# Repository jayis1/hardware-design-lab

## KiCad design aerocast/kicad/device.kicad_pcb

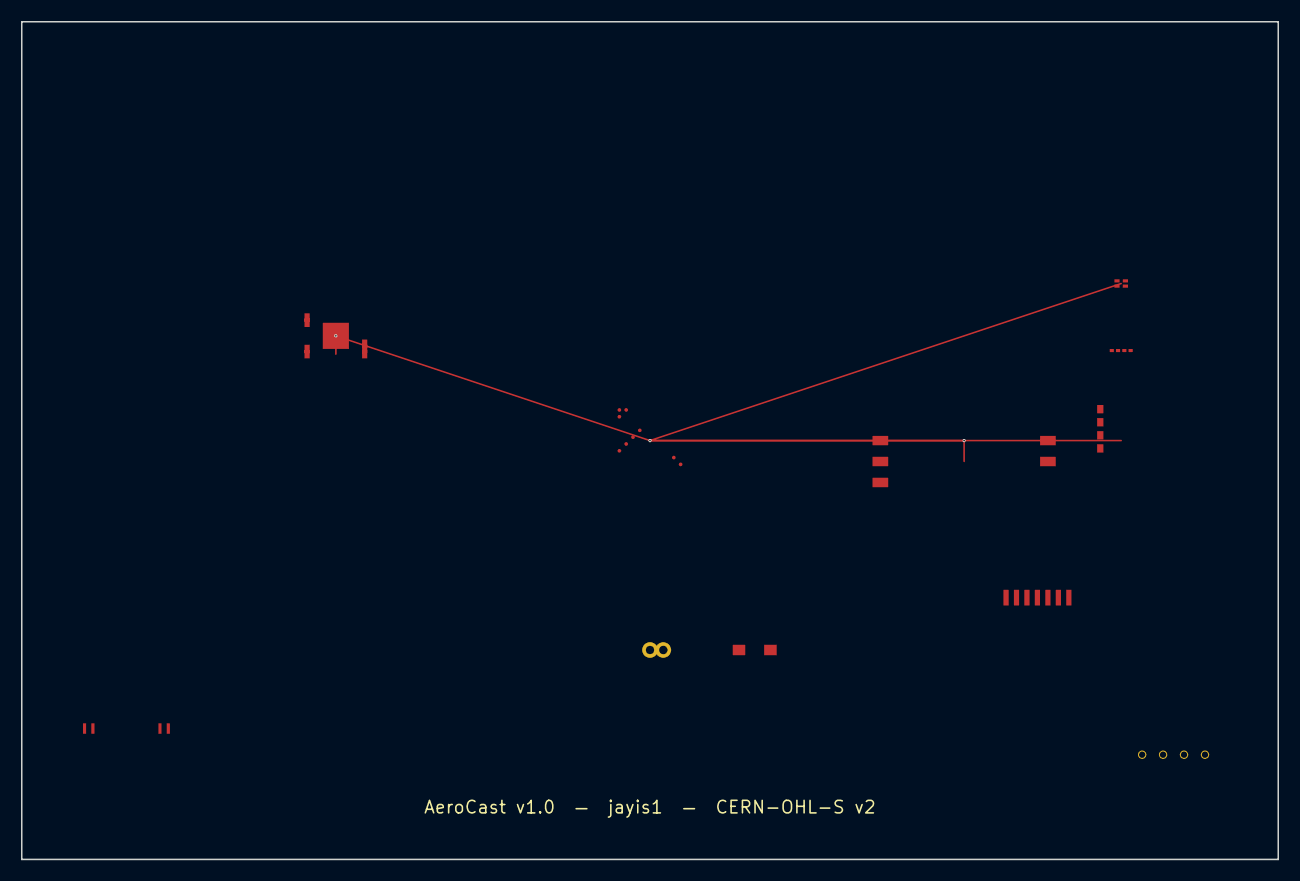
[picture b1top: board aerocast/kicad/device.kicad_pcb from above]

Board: 4 copper layers, 120.0 x 80.0 mm, 11 parts (0 on the bottom side), 9 nets.

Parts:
D1: 650nm_50mW; TO-18_3Pin
D2: 340nm_300mW; LED_3528
DISP1: ST7789V_240x320; ST7789V_2.4in_FPC_10pin
J1: USB-C; USB_C_Receptacle_HRO_TYPE-C-31-M-12
J4: Anemometer_RS485; JST_PH_B4B-PH-K_1x04_P2.00mm_Vertical
U1: STM32H7A3VIT6; UFBGA-176_10x10mm_P0.65mm
U2: ESP32-C6-MINI-2U
U3: LTC2351-14; QFN-32-1EP_5x5mm_P0.5mm
U4: SHT45; Sensirion_DFN-4-1EP_1.5x1.5mm_P0.5mm
U5: BMP390; Bosch_LGA-10_2.5x2.5mm_P0.6mm
U6: SDP810-500Pa; Sensirion_SDP8xx_DFN-8_5x8mm_P1.25mm

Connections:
+3V3: DISP1.1, U1.A2, U2.1, U4.1, U5.1, U6.1
+5V: D1.1, J1.A4, J1.B4, J4.3
GND: D1.2, D2.2, DISP1.2, J1.A1, J1.B9, J4.4, U1.A1, U2.2, U2.5, U3.2, U3.33, U4.4, U5.5, U6.4
I2C1_SCL: U1.M3, U4.2, U5.2
I2C1_SDA: U1.N4, U4.3, U5.3
SPI1_MISO: U1.L2, U3.11
SPI1_SCK: U1.K1, U3.10
USART2_RX: U1.J9, U2.3
USART2_TX: U1.H10, U2.4

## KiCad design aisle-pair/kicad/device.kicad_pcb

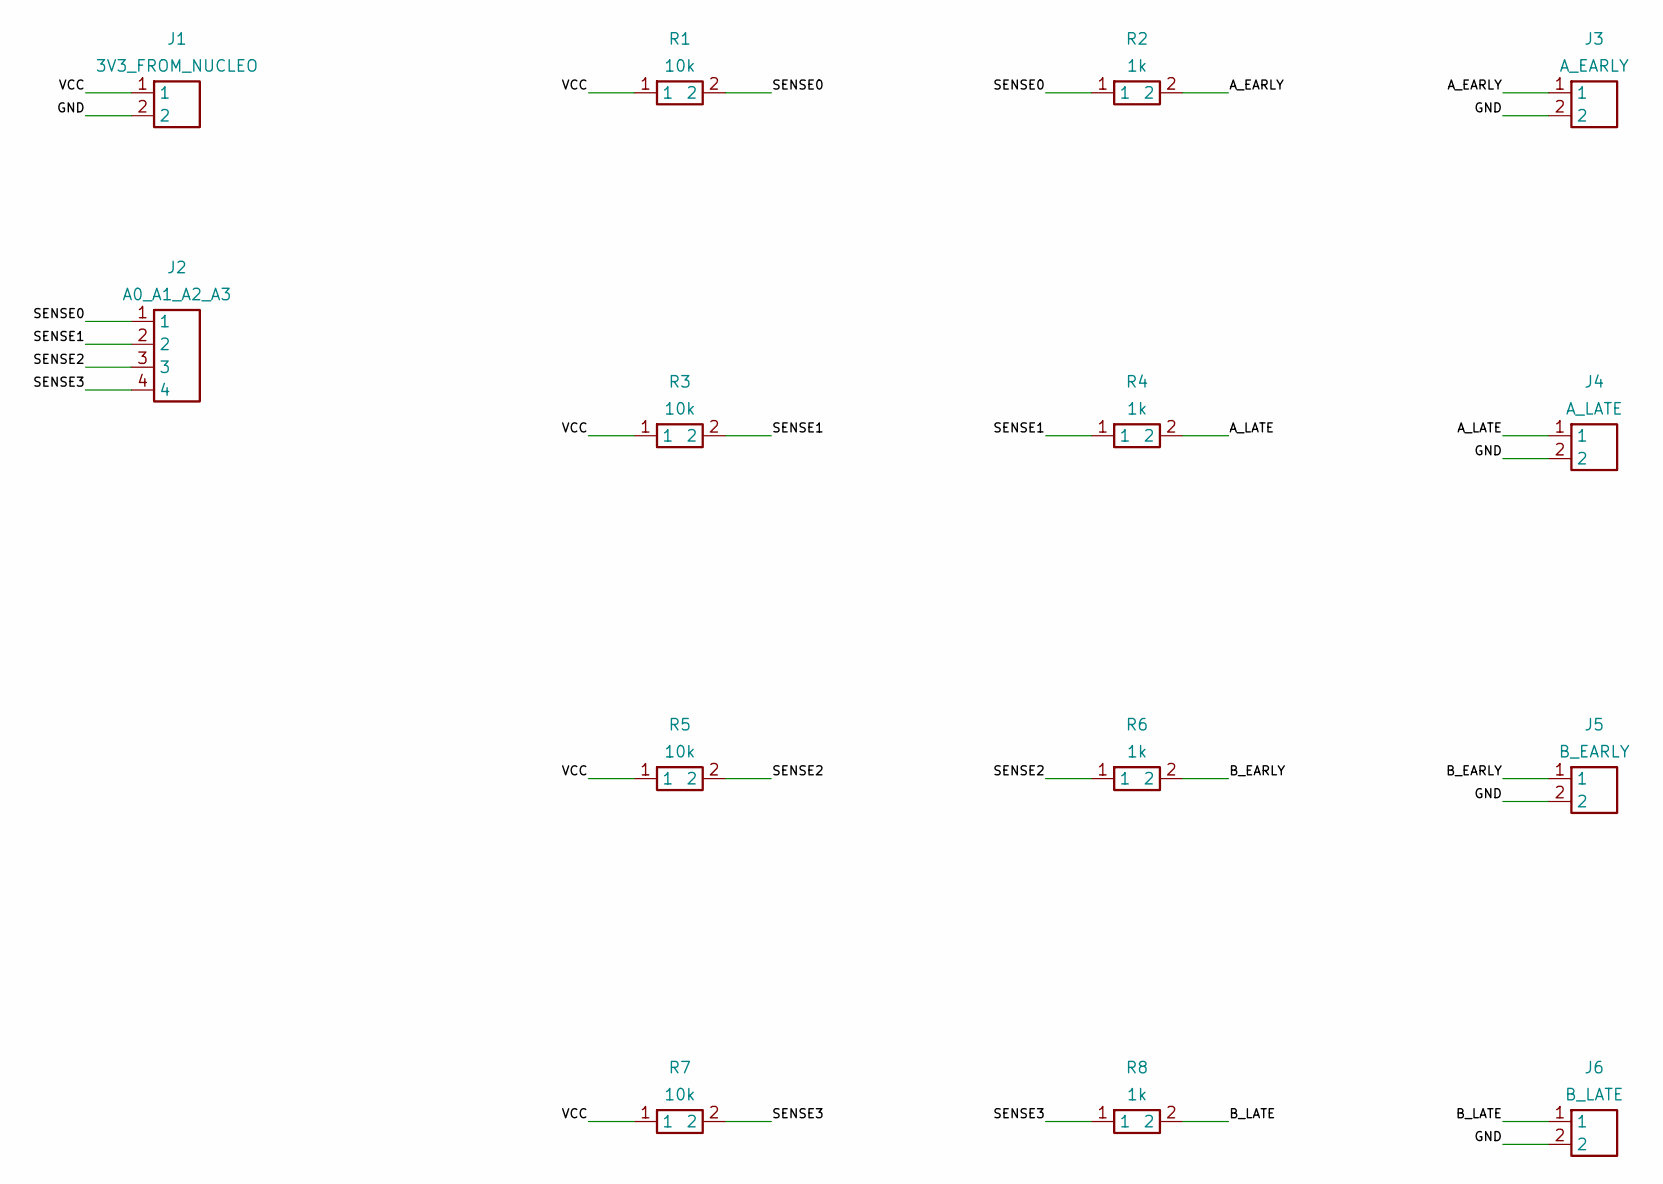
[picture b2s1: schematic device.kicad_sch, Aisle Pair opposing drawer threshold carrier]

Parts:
J1: 3V3_FROM_NUCLEO; PinHeader_1x02_P2.54mm_Vertical
J2: A0_A1_A2_A3; PinHeader_1x04_P2.54mm_Vertical
J3: A_EARLY; PinHeader_1x02_P2.54mm_Vertical
J4: A_LATE; PinHeader_1x02_P2.54mm_Vertical
J5: B_EARLY; PinHeader_1x02_P2.54mm_Vertical
J6: B_LATE; PinHeader_1x02_P2.54mm_Vertical
R1, R3, R5, R7: 10k; R_Axial_DIN0207_L6.3mm_D2.5mm_P7.62mm_Horizontal
R2, R4, R6, R8: 1k; R_Axial_DIN0207_L6.3mm_D2.5mm_P7.62mm_Horizontal

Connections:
A_EARLY: J3.1, R2.2
A_LATE: J4.1, R4.2
B_EARLY: J5.1, R6.2
B_LATE: J6.1, R8.2
GND: J1.2, J3.2, J4.2, J5.2, J6.2
SENSE0: J2.1, R1.2, R2.1
SENSE1: J2.2, R3.2, R4.1
SENSE2: J2.3, R5.2, R6.1
SENSE3: J2.4, R7.2, R8.1
VCC: J1.1, R1.1, R3.1, R5.1, R7.1

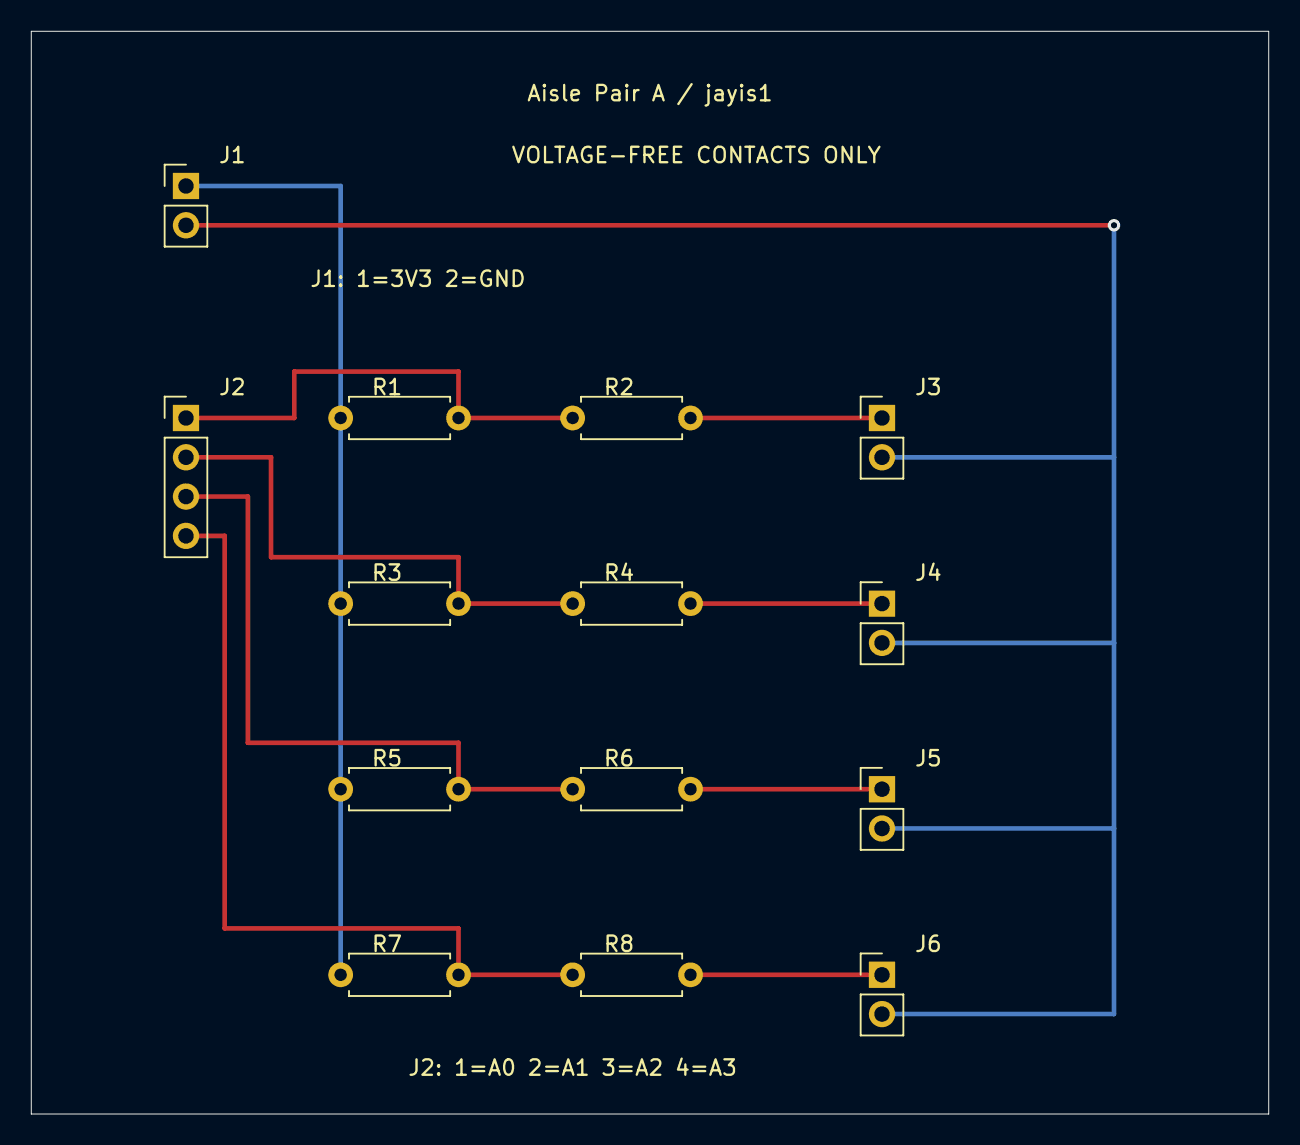
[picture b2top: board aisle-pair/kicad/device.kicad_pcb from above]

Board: 2 copper layers, 80.0 x 70.0 mm, 14 parts (0 on the bottom side), 10 nets.

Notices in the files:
aerocast/kicad/device.kicad_pcb:
Copyright (C) 2026 jayis1
License: CERN-OHL-S v2
AeroCast v1.0  —  jayis1  —  CERN-OHL-S v2
aerocast/kicad/device.kicad_sch:
Author: jayis1 — Copyright (C) 2026 jayis1
